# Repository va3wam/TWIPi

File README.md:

# TWIPi
This repository contains all the information on the fourth iteration of the SegbotSTEP family of robot designs. This repository contains C++ source code intended to run on the Adafruit Huzzah32 development board; Java code intended to run on a remote client such as a MAC or PC; EagleCAD schematic and layout files containing the circuit designs of the robot; Fusion 360 files (or pointers to those files on the AutoCAD cloud) used to mill the robot chassis; and all the libraries used by the IDEs that make up the tool chain used to create the robot.  

## Getting Started

Full details about this project can be read on our [wiki](https://github.com/va3wam/TWIPi/wiki). 

### Prerequisites

In order to make use of the robot circuit board and schematic diagrams you will need AutoCAD's EagleCAD application. In order to make use of the CAD and CAM diagrams of the robot chassis you will need AutoCAD's Fusion 360 application. From a software perspective, the Java and C++ (Arduino) code was written using Microsoft's Visual Source Code IDE.

### SOC Hardware Compatability

The Arduino C++ code was written to run on the Espressif ESP WROOM32 "Software On a Chip" (SOC). The development board used for this SOC is the Adafruit Huzzah32 featherboard.  

```
Note that this code will NOT run on an ESP8266. 
```

### Other Hardware Compatability

Aside from the code and development you will need to build a TWIPi compatible chassis and PCB. This
repository has EagleCAD diagrams to help you build the PCB. Also included are Fusion360 
CAD/CAM diagrams and associated GCODE for a Tormach 770 CNC mill to create the robot chassis. 
Full details for this project are located on the wiki associated with this repository.

### Installing

There are numerous tutorials on how to install Arduino code onto an ESP WROOM32 from Visual Source Code. Details and relevant links can be found on this respositories wiki. 

## Running the tests

At this time there are no automated tests for this system

## Deployment

This Arduino code was developed using the following set up.

### Built With

* [Visual Studio Code](https://code.visualstudio.com/) - The IDE
* [Platformio](https://platformio.org/) - Editor plugin
* Library Framework - Arduino
* Hardware platform - espressif32
* Board - Adafruit Huzzah32 featherboard
### Arduino Libraries
The following additional libraries are used in the Arduino C++ code:
* https://github.com/Pedroalbuquerque/ESP32WebServer
* https://github.com/Links2004/arduinoWebSockets
* https://github.com/marcoschwartz/LiquidCrystal_I2C
* https://github.com/bblanchon/ArduinoJson

## Contributing

This project is being developed by a couple of buddies. We are tracking the tasks for this
effort in a series of small [projects](https://github.com/va3wam/TWIPi/projects).

## Versioning

We use [SemVer](http://semver.org/) for versioning. For the versions available, see the [tags on this repository](https://github.com/va3wam/TWIPi/branches/all). 

## Authors

* [Doug](https://github.com/nerdoug) - *PID and motor control logic and circuit diagrams*
* [Andrew](https://github.com/va3wam) - *Initial code porting from ESP128 to ESP32, remote Java client and CAD/CAM designs* 

See also the list of [contributors](https://github.com/va3wam/TWIPi/graphs/contributors) who participated in this project.

## License

This project has no licensing terms. Use at own risk, no support provided. 

## Acknowledgments

* Big thanks to [Brokking](http://www.brokking.net/yabr_main.html) for his excellent tutorial which really helped us get going
* Thanks to the folks who developed the libraries we have made use of for I2C, JSON, Web and Websockets

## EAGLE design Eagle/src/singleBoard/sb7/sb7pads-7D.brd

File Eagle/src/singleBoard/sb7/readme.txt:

SB7 is a double sided board with all parts of previous SB6 abd PL2 boards except power regulators.
Pushbuttons and external USB Jack are on "solder" side of main board.
In more detail, when you can read the layout version number 7B in the top left corner:
-most components, including the CPU, IMU, motor controllers are on the side of the board facing you, the "front"
-the 4 pushbuttons and USB jack on the left side of the board are on the back, away from you
 (the board is rotated when mounted in bot, so the row of pushbuttons is on the top)
-the red traces are on the back of the board, and connect the components on the front of the board
-the blue traces are on the front of the board, and connect components on the back of the board (pushbuttons & USB jack)
-connections that use VIAs have sections on both sides of the board

There are about 19 simulated VIAs which should be changed to real VIAs if board manufacture is outsourced

7A version layout
-pushbuttons are slightly off centre
-there's a ground test point, but no 3.3, 5, or 12V test points
-board is slightly bigger - 3.90 by 3.95 inches
-mounting holes have been moved - do they have enough clearance?
-the 2 power connectors are faked with 0.2 inch contacts. should get real part references
- battery connection is a 2 conductor cable near back of 4th pushbutton
- regulator connections (in and out) are a 5 conductor cable near back of 1st pushbutton
-there are no power protection diodes. It's assumed that power connectors are keyed
-resistor R4 is used as a VIA and needs to be soldered on both sides
-battery ground is intentionally not connected to regulator output ground
-the grounds for 12 and 5V regulator output are bridged at the regulators and have a common wire
 to the main board called RO-12VG ("regulator output, 12V regulator, ground")

7B version layout
-push buttons centred better
-see if there is an available short USB console cable, and change header to match it.

7C version layout
-all vias have been converted to true vias, not manual ones
-resistor R4 no longer functions as a via, & normal soldering is OK
-power connectors remain unresolved. 
    - may need to move capacitor to allow right angled connectors. 
	- may be too tight for them anyway, unless they face outwards?
-crossed wires for stepper driver STEPDRV2 on board, so all stepper wiring is straight thru

References on Wire Gauge / Current capacity

https://www.powerstream.com/Wire_Size.htm    (24AWG for 3.5 amps, stranded?)
https://www.jst.fr/doc/jst/pdf/current_rating.pdf   (22 AWG for 3.0A)
https://www.multicable.com/resources/reference-data/current-carrying-capacity-of-copper-conductors/
https://www.solaris-shop.com/content/American%20Wire%20Gauge%20Conductor%20Size%20Table.pdf
https://xtronics.com/wiki/Wire-Gauge_Ampacity.html
https://www.gore.com/IndustrialCableConfigurator/popup_hfr_wirespecs.html
http://www.learningaboutelectronics.com/Articles/Wire-gauge.php
https://www.coonerwire.com/amp-chart/
https://en.wikipedia.org/wiki/American_wire_gauge

Approach: Solder wires to board with pre-installed connectors at ends
https://www.bc-robotics.com/shop/2-wire-inline-connector/
https://www.bc-robotics.com/shop/2-pin-jst-sm-plug-receptacle-cable-set/
https://www.creatroninc.com/product/3-pin-js-m-wire-assembly/
https://www.creatroninc.com/product/3-pin-js-f-wire-assembly/
https://www.robotshop.com/en/sfe-130mm-wire-jst-blk-red.html
https://www.robotshop.com/en/sfe-100mm-wire-jst-blk-blue.html

https://canada.newark.com/w/c/connectors/wire-to-board-connectors/prl/results?st=jst%20cables
https://canada.newark.com/w/c/cable-wire-cable-assemblies/cable-assemblies/prl/results?st=jst%20cables

https://www.amazon.ca/URBEST-10Pairs-Female-Connector-Battery/dp/B01M13PMIU
https://solarbotics.com/product/14226

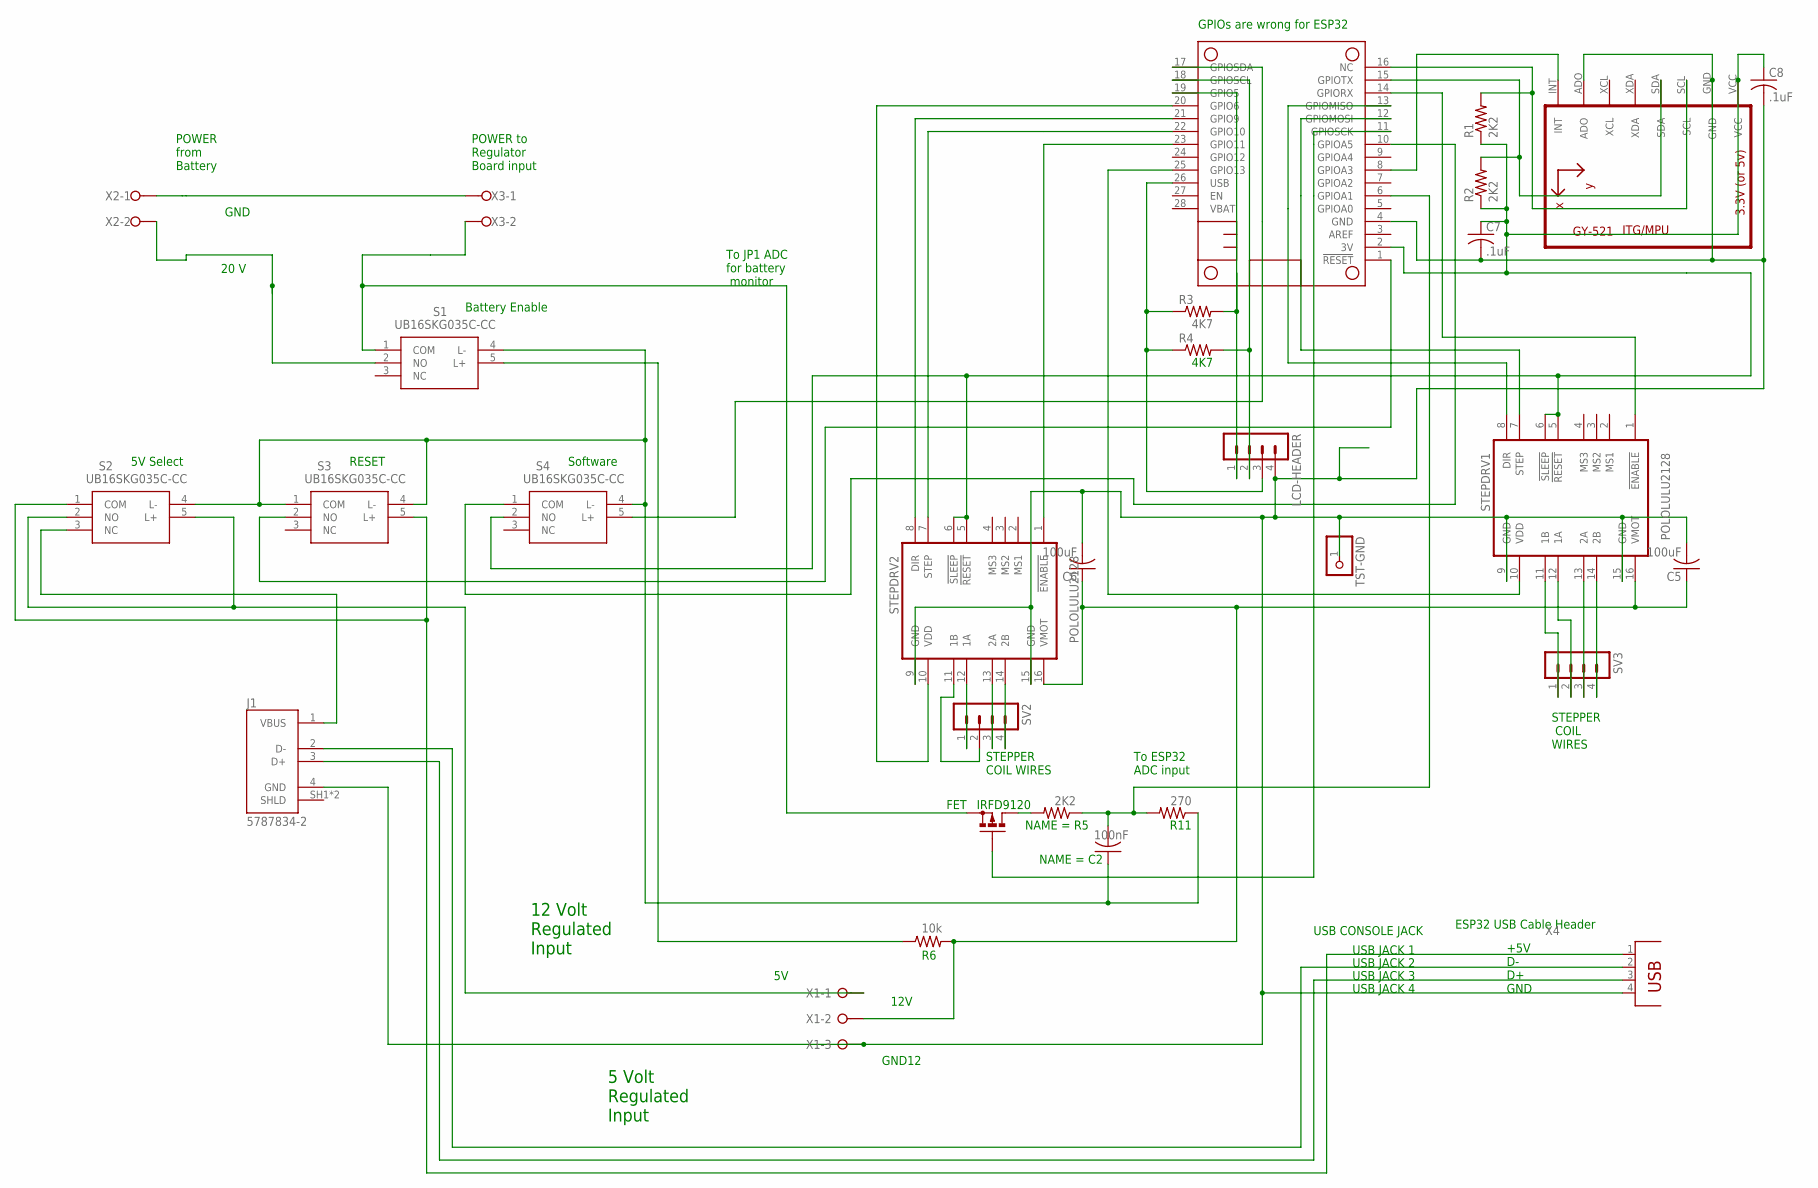
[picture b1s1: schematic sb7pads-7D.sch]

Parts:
C2: 100nF; C050-025X075
C5, C6: 100uF; C050-024X044
C7, C8: .1uF; C050-024X044
FET: IRFD9120; C370-01
J1: 5787834-2; TE_5787834-2
LCD-HEADER: MA04-1
MS2: FEATHERWING_NOHOLES
R1, R2: 2K2; 0309/12
R3, R4: 4K7; 0309/12
R5: 2K2; 0207/10
R6: 10k; 0207/10
R11: 270; 0207/10
S1, S2, S3, S4: UB16SKG035C-CC; UB16SKG035CCC
STEPDRV1, STEPDRV2: POLOLULU2128
SV2, SV3: MA04-1
TST-GND: 1X01
U1: GY-521MPU6050; GY-521
X1: W237-3E
X2, X3: W237-02P; W237-132
X4: PN87520

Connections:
3V: C7.1, C8.1, MS2.2 (3V), R1.1, R2.1, S4.2 (NO), STEPDRV1.5 (!RESET), STEPDRV1.6 (!SLEEP), STEPDRV2.5 (!RESET), STEPDRV2.6 (!SLEEP), U1.VCC
unnamed: MS2.25 (GPIO13), STEPDRV1.10 (VDD)
unnamed: FET.G, MS2.11 (GPIOSCK)
unnamed: S1.2 (NO), X2.2
unnamed: MS2.1 (!RESET), S3.2 (NO)
unnamed: MS2.21 (GPIO9), STEPDRV2.8 (DIR)
unnamed: FET.S, S1.1 (COM), X3.2
unnamed: MS2.14 (GPIORX), STEPDRV1.1 (!ENABLE)
unnamed: STEPDRV2.14 (2B), SV2.4
unnamed: STEPDRV2.12 (1A), SV2.1
unnamed: LCD-HEADER.1, MS2.19 (GPIO5), R3.2
unnamed: STEPDRV2.13 (2A), SV2.3
unnamed: STEPDRV2.11 (1B), SV2.2
unnamed: MS2.8 (GPIOA3), U1.INT
unnamed: MS2.12 (GPIOMOSI), STEPDRV1.7 (STEP)
unnamed: STEPDRV1.14 (2B), SV3.4
unnamed: MS2.16 (NC), R1.2, U1.SCL
unnamed: STEPDRV1.13 (2A), SV3.3
unnamed: STEPDRV1.12 (1A), SV3.2
unnamed: STEPDRV1.11 (1B), SV3.1
unnamed: X2.1, X3.1
unnamed: J1.2 (D-), X4.2
unnamed: J1.3 (D+), X4.3
unnamed: MS2.13 (GPIOMISO), STEPDRV1.8 (DIR)
unnamed: MS2.15 (GPIOTX), R2.2, U1.SDA
unnamed: C5.2, C6.2, C7.2, C8.2, J1.4 (GND), LCD-HEADER.4, MS2.4 (GND), STEPDRV1.9 (GND), STEPDRV1.15 (GND), STEPDRV2.9 (GND), STEPDRV2.15 (GND), TST-GND.1, U1.ADO, U1.GND, X1.3, X4.4
unnamed: S2.2 (NO), S2.5 (L+), X1.1
unnamed: MS2.17 (GPIOSDA), S4.5 (L+)
unnamed: C2.2, MS2.6 (GPIOA1), R5.1, R11.2
unnamed: R6.1, S1.5 (L+)
unnamed: S2.1 (COM), S3.5 (L+), X4.1
unnamed: MS2.22 (GPIO10), STEPDRV2.7 (STEP)
unnamed: LCD-HEADER.2, MS2.18 (GPIOSCL), R4.2
unnamed: MS2.20 (GPIO6), STEPDRV2.10 (VDD)
unnamed: MS2.23 (GPIO11), STEPDRV2.1 (!ENABLE)
unnamed: MS2.10 (GPIOA5), S4.1 (COM)
unnamed: C5.1, C6.1, R6.2, STEPDRV1.16 (VMOT), STEPDRV2.16 (VMOT), X1.2
unnamed: J1.1 (VBUS), S2.3 (NC)
unnamed: FET.D, FET.D1 (D), R5.2
unnamed: C2.1, R11.1, S1.4 (L-), S2.4 (L-), S3.1 (COM), S3.4 (L-), S4.4 (L-)
USB: LCD-HEADER.3, MS2.26 (USB), R3.1, R4.1

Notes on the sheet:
GPIOs are wrong for ESP32
STEPPER COIL WIRES
12V
GND12
ESP32 USB Cable Header
STEPPER COIL WIRES
To ESP32 ADC input
+5V D- D+ GND
To JP1 ADC for battery monitor
USB CONSOLE JACK
USB JACK 1
USB JACK 2
USB JACK 3
USB JACK 4
POWER from Battery
POWER to Regulator Board input
20 V
GND
Battery Enable
5V Select
RESET
Software
12 Volt Regulated Input
5 Volt Regulated Input

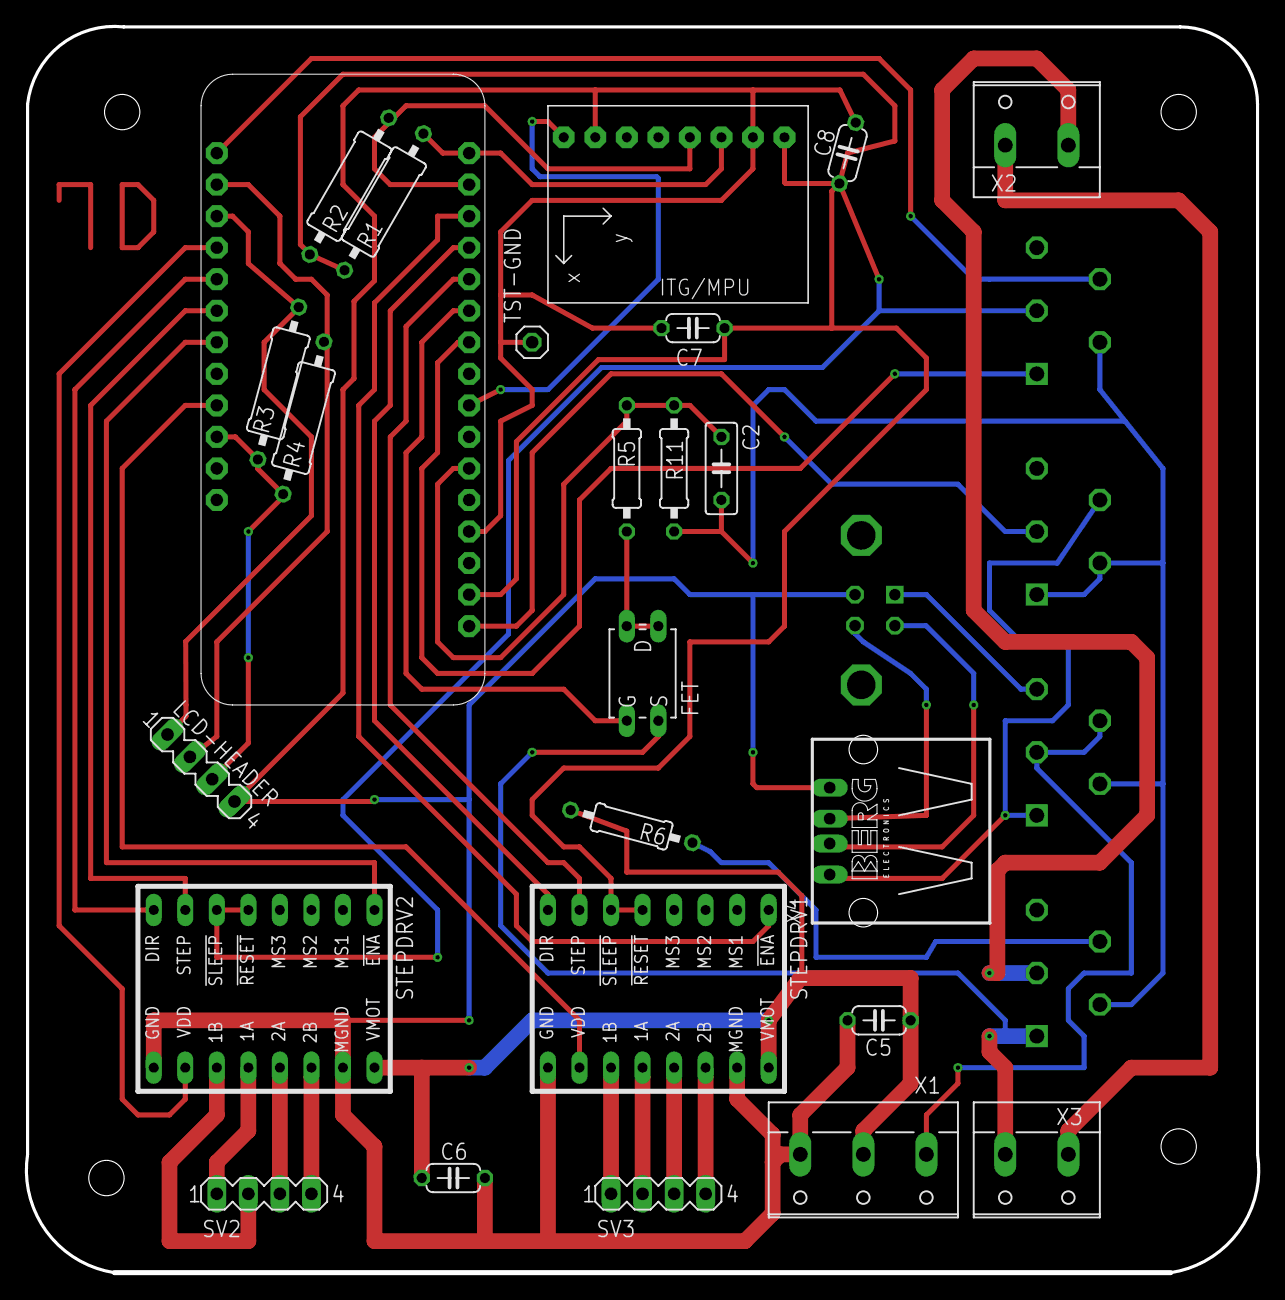
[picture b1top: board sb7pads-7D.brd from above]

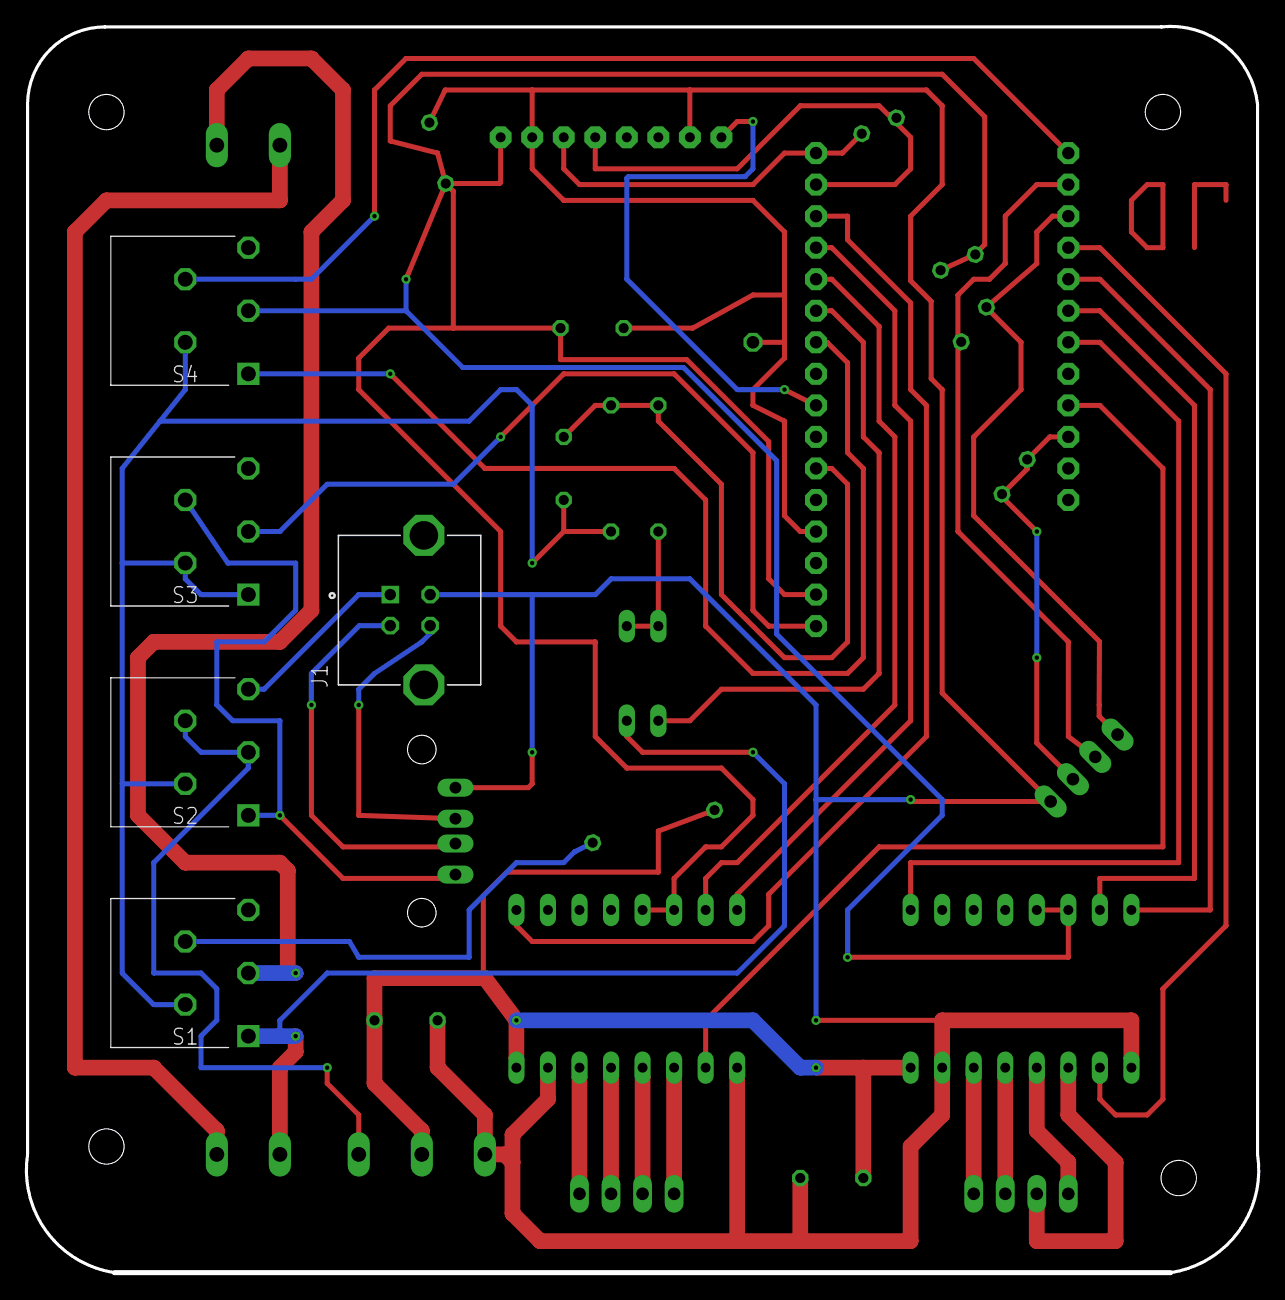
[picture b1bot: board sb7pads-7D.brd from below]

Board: 2 copper layers, 99.3 x 100.4 mm, 30 parts (5 on the bottom side), 41 nets.

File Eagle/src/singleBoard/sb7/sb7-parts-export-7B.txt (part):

Partlist exported from C:/dae/GitHub/VA3WAM/TWIPi/Eagle/src/singleBoard/sb7/sb7pads.sch at 2020-01-23 9:33 PM

Part       Value               Device              Package             Description                                                                        ALLIED_NUMBER ALLIED_PRICE-STOCK                                              COMMENT   DESCRIPTION                                                                          DIGI-KEY_PART_NUMBER DIGI-KEY_PURCHASE_URL                                                                                                                                              EU_ROHS_COMPLIANCE HEIGHT MANUFACTURER_NAME MANUFACTURER_PART_NUMBER MF              MOUSER_PART_NUMBER MOUSER_PRICE-STOCK                                                  MP        MPN OC_FARNELL OC_NEWARK PACKAGE RS_PART_NUMBER RS_PRICE-STOCK SPICEPREFIX TE_PURCHASE_URL                                                                                                                                                              
BO-20VG                        PINHD-1X1           1X01                PIN HEADER                                                                                                                                                                                                                                                                                                                                                                                                                                                                                                                                                                                                                                                                                                                                                                                                                                                                                            
BO-20VP                        PINHD-1X1           1X01                PIN HEADER                                                                                                                                                                                                                                                                                                                                                                                                                                                                                                                                                                                                                                                                                                                                                                                                                                                                                            
C2         100nF               C-US050-025X075     C050-025X075        CAPACITOR, American symbol                                                                                                                                                                                                                                                                                                                                                                                                                                                                                                                                                                                                                                                                                   C                                                                                                                                                                                        
C5         100uF               C-US050-024X044     C050-024X044        CAPACITOR, American symbol                                                                                                                                                                                                                                                                                                                                                                                                                                                                                                                                                                                                                                                                                   C                                                                                                                                                                                        
C6         100uF               C-US050-024X044     C050-024X044        CAPACITOR, American symbol                                                                                                                                                                                                                                                                                                                                                                                                                                                                                                                                                                                                                                                                                   C                                                                                                                                                                                        
C7         .1uF                C-US050-024X044     C050-024X044        CAPACITOR, American symbol                                                                                                                                                                                                                                                                                                                                                                                                                                                                                                                                                                                                                                                                                   C                                                                                                                                                                                        
C8         .1uF                C-US050-024X044     C050-024X044        CAPACITOR, American symbol                                                                                                                                                                                                                                                                                                                                                                                                                                                                                                                                                                                                                                                                                   C                                                                                                                                                                                        
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
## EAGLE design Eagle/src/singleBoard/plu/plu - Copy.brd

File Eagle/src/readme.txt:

This is where the Schematic (SCH) and Layout (BRD) files for Eagle PCBs go. the file testToolOffsetModForFlatCAMfiles.nc contains manually crafted g-code to test ATC control for jobs created in FlatCAM. See TWIPi\Eagle\docConvertFlatCAMgcode.ods for the procedure for inserting these codes into FlatCAM generated G-code.

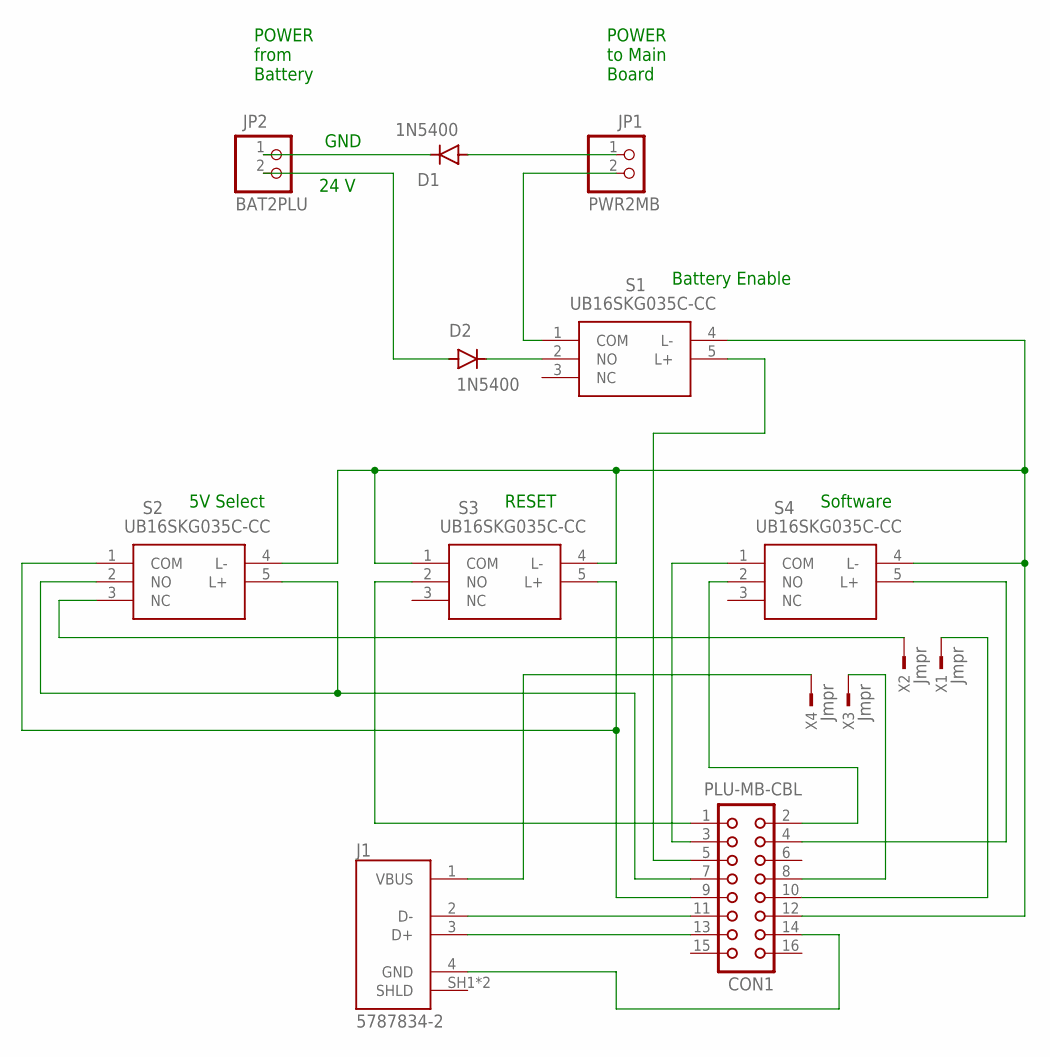
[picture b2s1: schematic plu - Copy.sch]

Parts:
CON1: PLU-MB-CBL; CON16
D1, D2: 1N5400; DO201-15
J1: 5787834-2; TE_5787834-2
JP1: PWR2MB; 1X02
JP2: BAT2PLU; 1X02
S1, S2, S3, S4: UB16SKG035C-CC; UB16SKG035CCC
X1, X2, X3, X4: Jmpr; TSW-101-XX-G-S

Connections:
unnamed: D1.A, JP1.1
unnamed: CON1.1, S3.2 (NO)
unnamed: D1.C, JP2.1
unnamed: D2.C, S1.2 (NO)
unnamed: D2.A, JP2.2
unnamed: JP1.2, S1.1 (COM)
unnamed: CON1.11, J1.2 (D-)
unnamed: J1.1 (VBUS), X4.1
unnamed: CON1.2, S4.2 (NO)
unnamed: CON1.3, S4.1 (COM)
unnamed: CON1.13, J1.3 (D+)
unnamed: CON1.4, S4.5 (L+)
unnamed: CON1.5, S1.5 (L+)
unnamed: CON1.14, J1.4 (GND)
unnamed: CON1.7, S2.2 (NO), S2.5 (L+)
unnamed: CON1.10, X1.1
unnamed: CON1.9, S2.1 (COM), S3.5 (L+)
unnamed: CON1.12, S1.4 (L-), S2.4 (L-), S3.1 (COM), S3.4 (L-), S4.4 (L-)
unnamed: S2.3 (NC), X2.1
unnamed: CON1.8, X3.1

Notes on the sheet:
POWER from Battery
POWER to Main Board
24 V
GND
Battery Enable
5V Select
RESET
Software

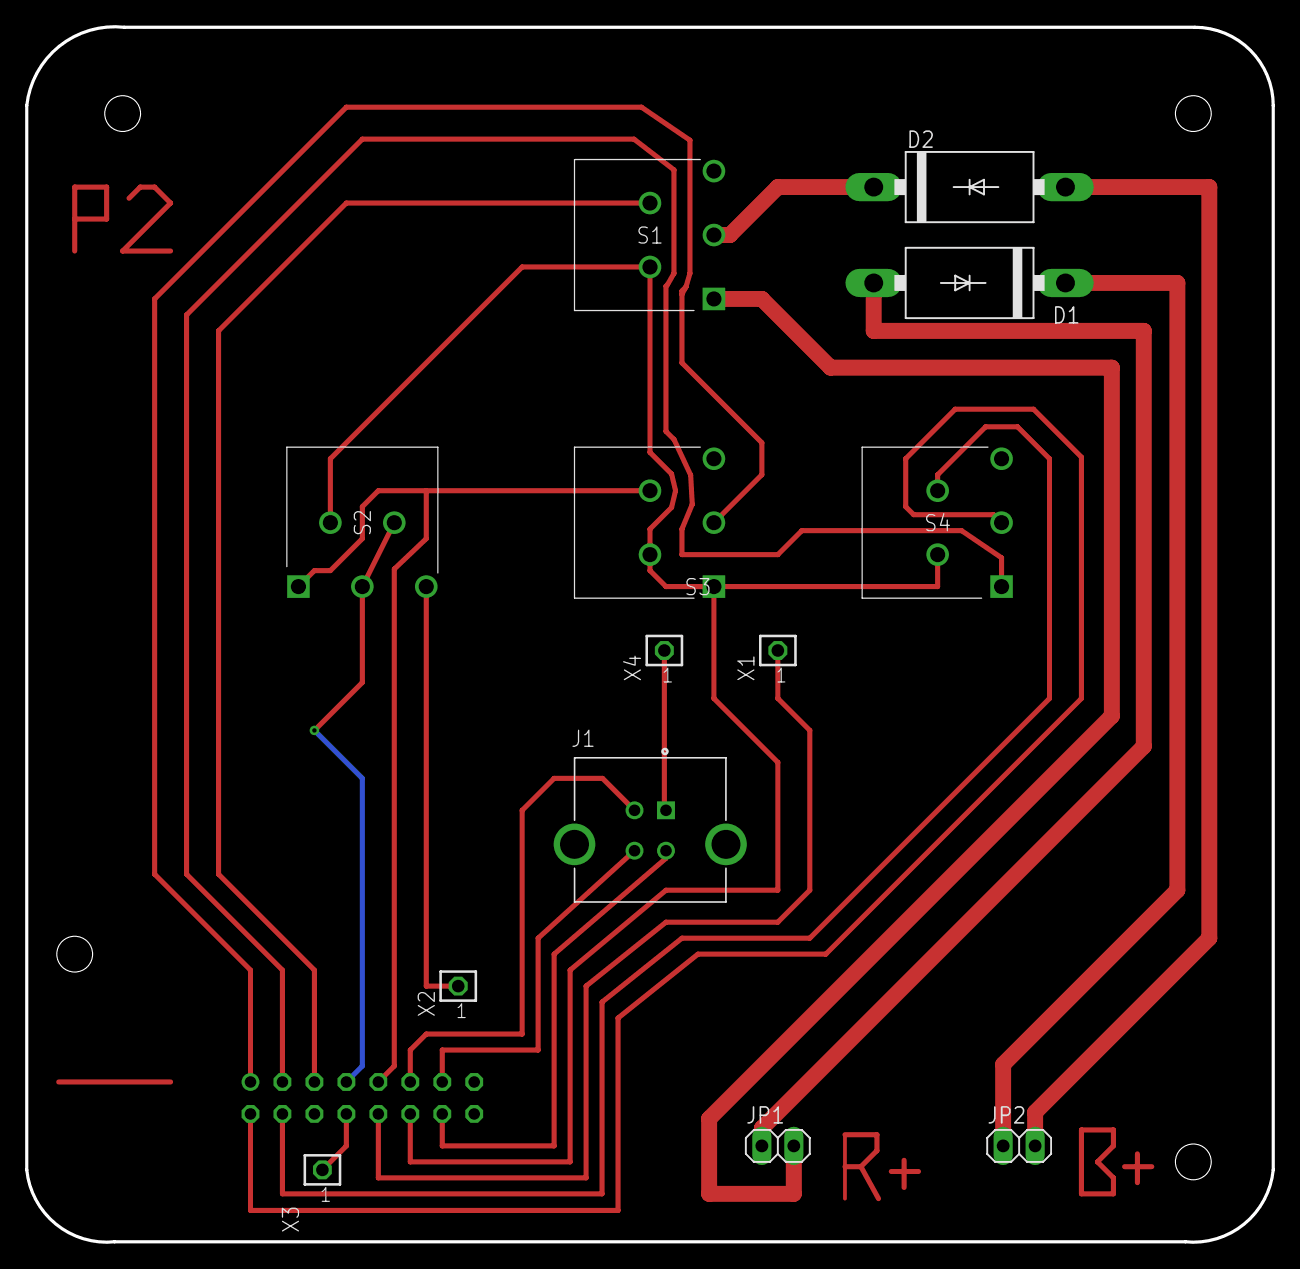
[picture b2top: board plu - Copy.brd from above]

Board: 2 copper layers, 99.1 x 96.6 mm, 14 parts (1 on the bottom side), 20 nets.

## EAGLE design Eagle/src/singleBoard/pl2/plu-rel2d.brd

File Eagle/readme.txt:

This is the directory where PCB files are placed

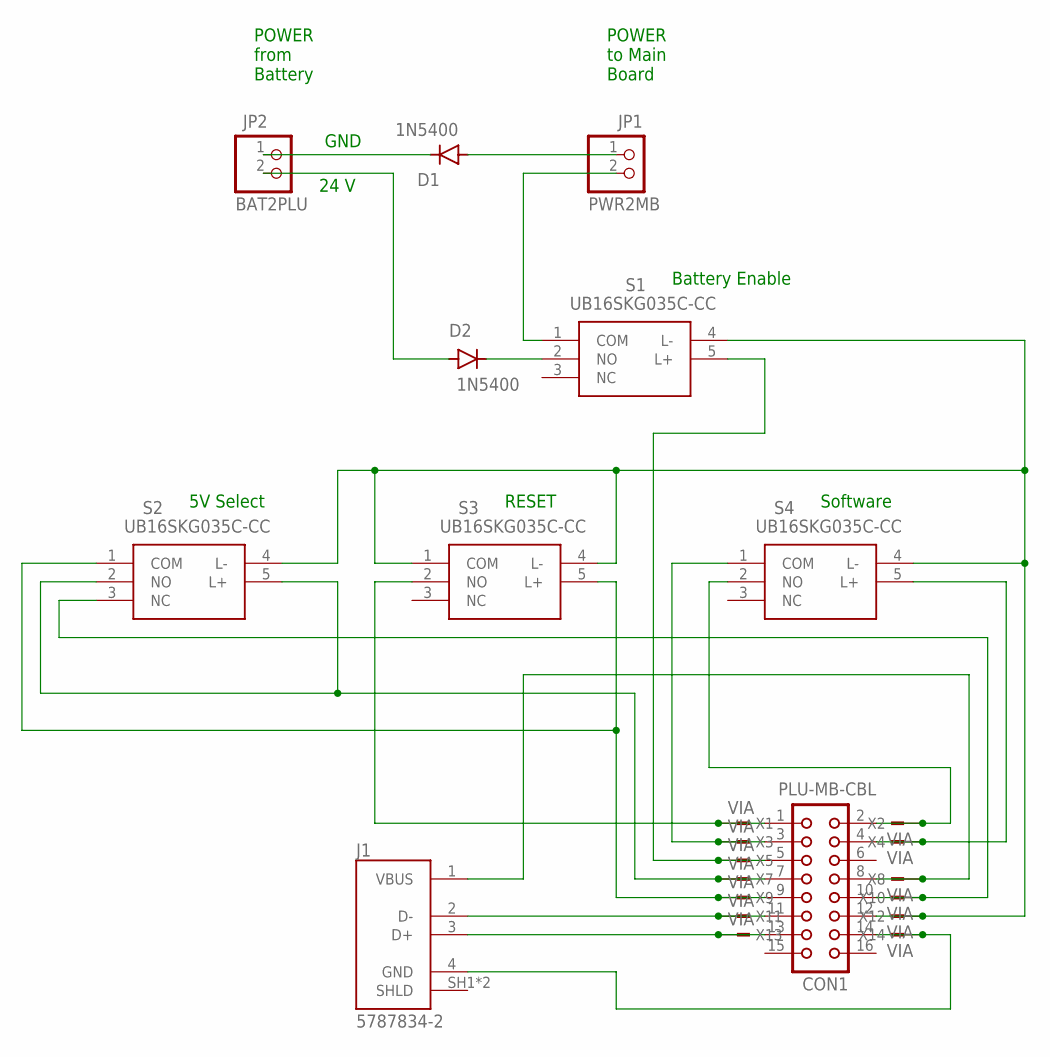
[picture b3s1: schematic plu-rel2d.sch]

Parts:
CON1: PLU-MB-CBL; CON16
D1, D2: 1N5400; DO201-15
J1: 5787834-2; TE_5787834-2
JP1: PWR2MB; 1X02
JP2: BAT2PLU; 1X02
S1, S2, S3, S4: UB16SKG035C-CC; UB16SKG035CCC
X1, X2, X3, X4, X5, X7, X8, X9, X10, X11, X12, X13, X14: VIA; TSW-101-XX-G-S

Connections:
unnamed: D1.A, JP1.1
unnamed: CON1.1, S3.2 (NO), X1.1
unnamed: D1.C, JP2.1
unnamed: D2.C, S1.2 (NO)
unnamed: D2.A, JP2.2
unnamed: JP1.2, S1.1 (COM)
unnamed: CON1.3, S4.1 (COM), X3.1
unnamed: CON1.2, S4.2 (NO), X2.1
unnamed: CON1.4, S4.5 (L+), X4.1
unnamed: CON1.8, J1.1 (VBUS), X8.1
unnamed: CON1.5, S1.5 (L+), X5.1
unnamed: CON1.7, S2.2 (NO), S2.5 (L+), X7.1
unnamed: CON1.9, S2.1 (COM), S3.5 (L+), X9.1
unnamed: CON1.10, S2.3 (NC), X10.1
unnamed: CON1.11, J1.2 (D-), X11.1
unnamed: CON1.13, J1.3 (D+), X13.1
unnamed: CON1.12, S1.4 (L-), S2.4 (L-), S3.1 (COM), S3.4 (L-), S4.4 (L-), X12.1
unnamed: CON1.14, J1.4 (GND), X14.1

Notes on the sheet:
POWER from Battery
POWER to Main Board
24 V
GND
Battery Enable
5V Select
RESET
Software

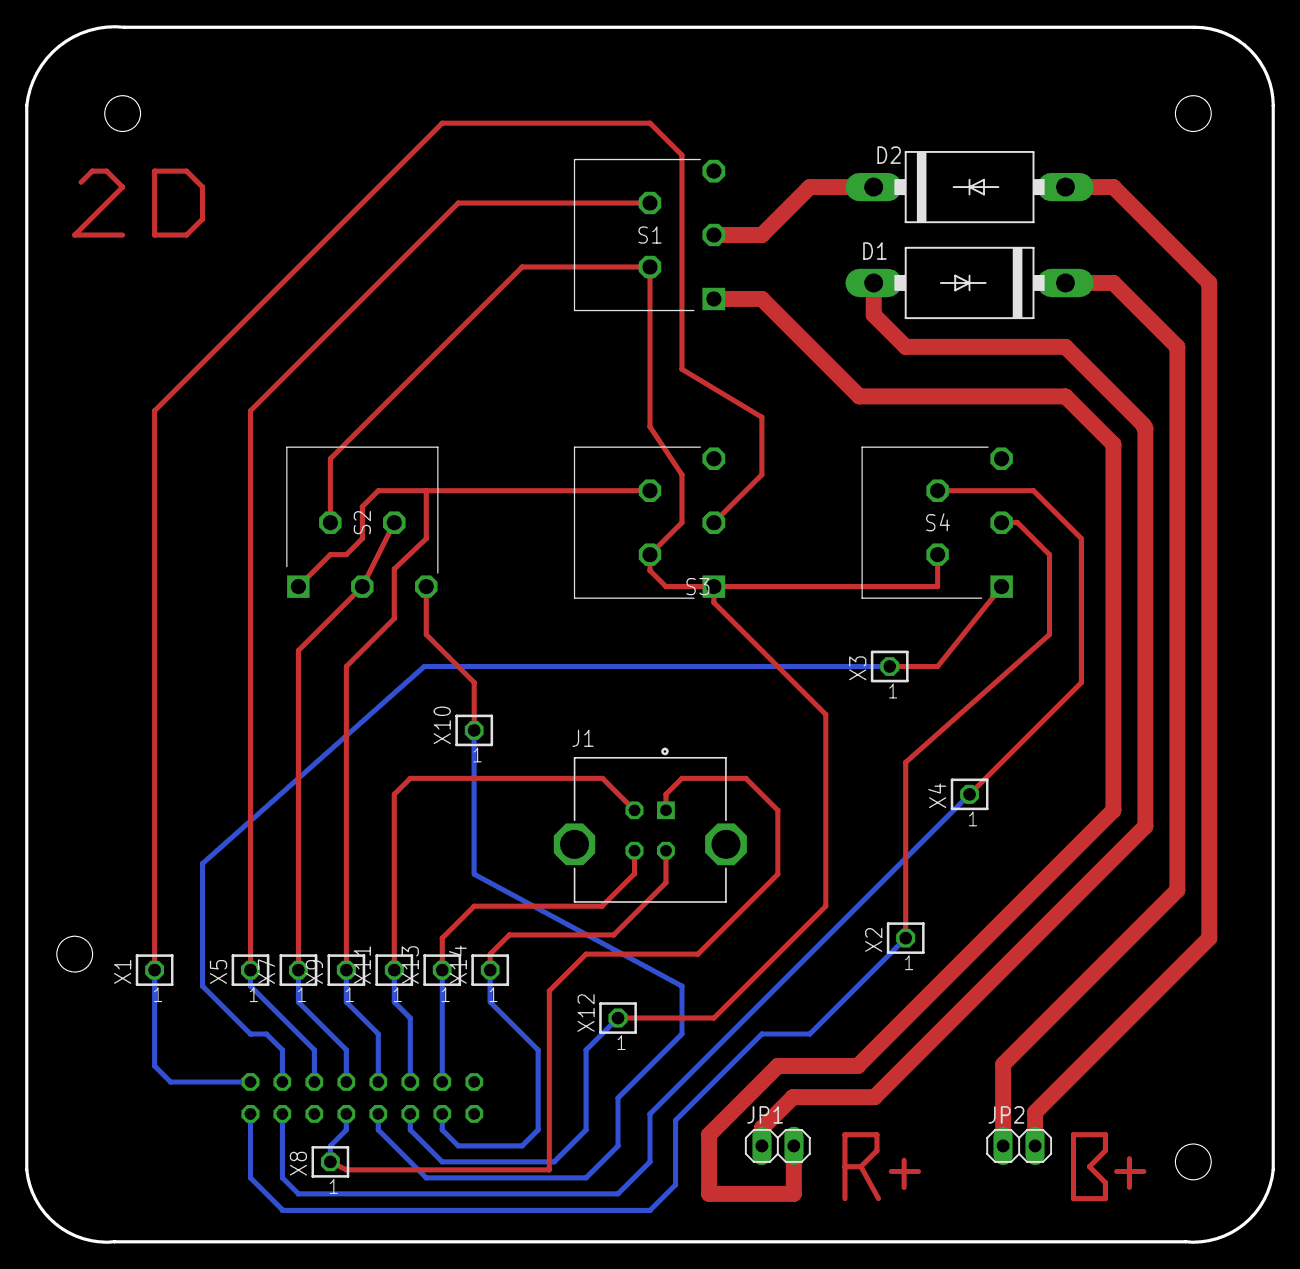
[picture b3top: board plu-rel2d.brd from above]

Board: 2 copper layers, 99.1 x 96.6 mm, 23 parts (1 on the bottom side), 18 nets.
